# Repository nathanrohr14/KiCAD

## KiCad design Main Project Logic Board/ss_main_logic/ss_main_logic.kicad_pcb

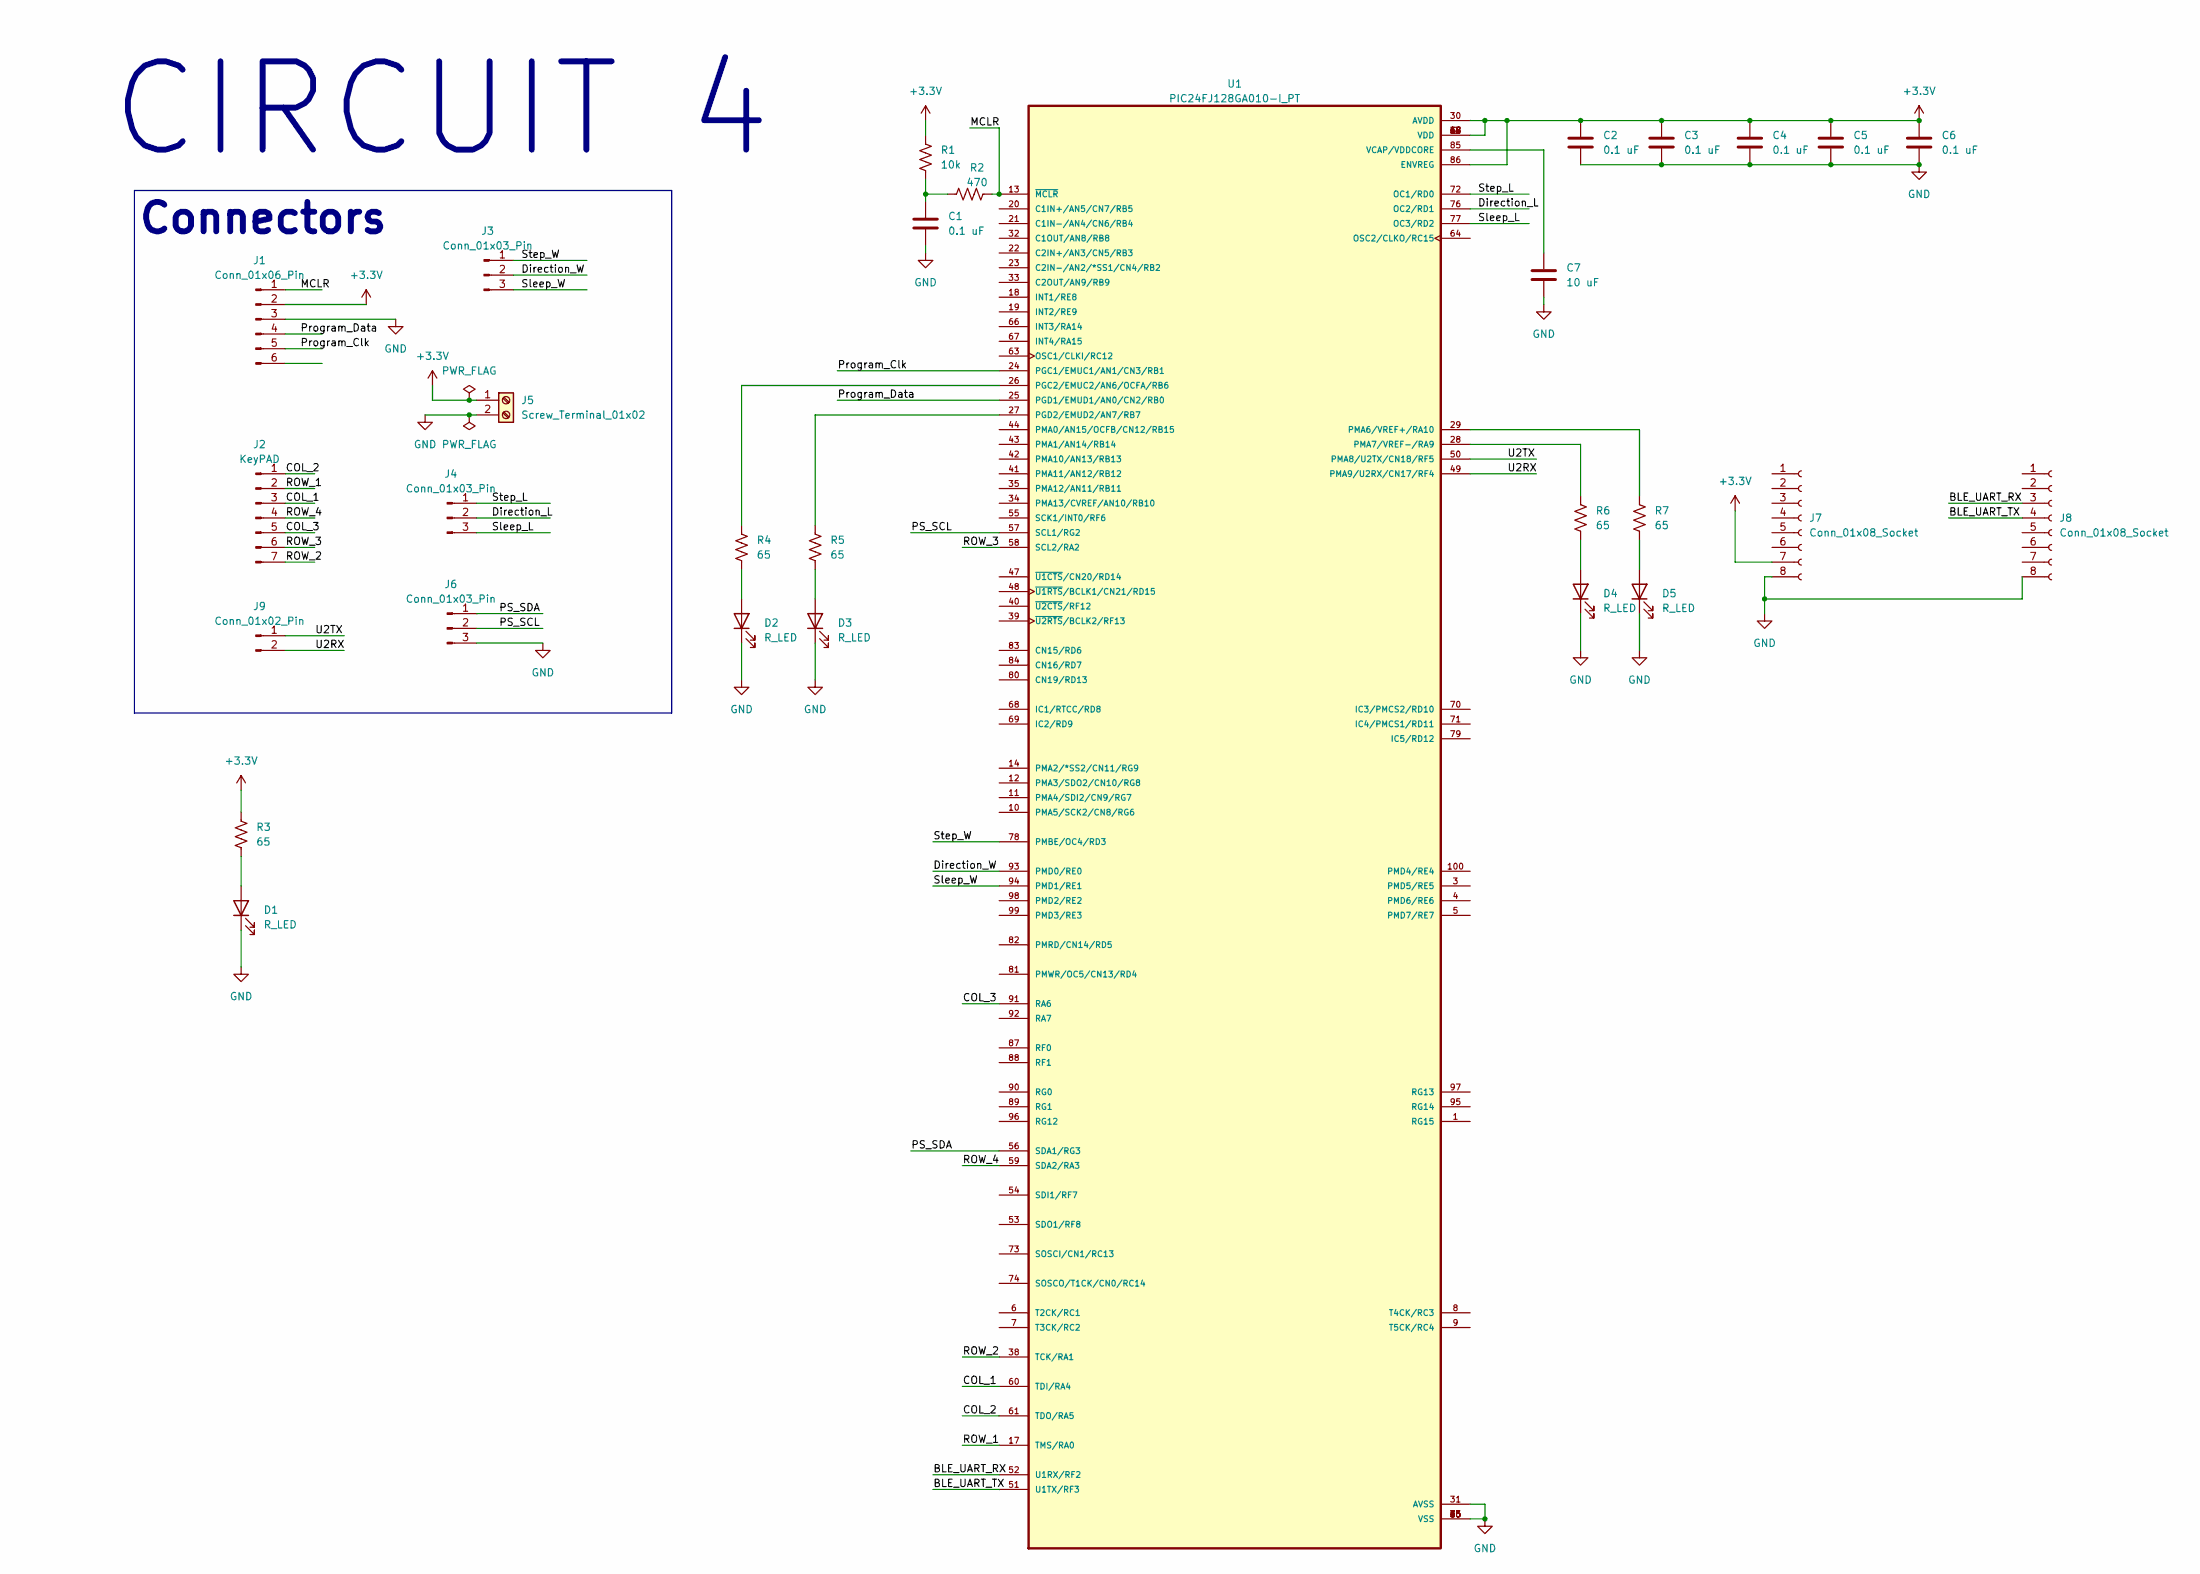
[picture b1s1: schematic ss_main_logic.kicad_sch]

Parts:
C1, C2, C3, C4, C5, C6: 0.1 uF; C_0603_1608Metric; LCSC C14663
C7: 10 uF; C_1206_3216Metric; LCSC C13585
D1, D2, D3, D4, D5: R_LED; LED_0603_1608Metric; LCSC C2286
J1: Conn_01x06_Pin; PinHeader_1x06_P2.54mm_Vertical
J2: KeyPAD; PinHeader_1x07_P2.54mm_Vertical
J3, J4, J6: Conn_01x03_Pin; PinHeader_1x03_P2.54mm_Vertical
J5: Screw_Terminal_01x02; 282837-2_TYC
J7, J8: Conn_01x08_Socket; PinSocket_1x08_P2.54mm_Vertical
J9: Conn_01x02_Pin; PinHeader_1x02_P2.54mm_Vertical
R1: 10k; R_0603_1608Metric
R2: 470; R_0603_1608Metric; LCSC C23179
R3, R4, R5, R6, R7: 65; R_1210_3225Metric; LCSC C11021
U1: PIC24FJ128GA010-I_PT; TQFP-100_14x14mm_P0.5mm; LCSC C638384

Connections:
+3.3V: C2.1, C3.1, C4.1, C5.1, C6.1, J1.2, J5.1, J7.7, R1.1, R3.1, U1.2 (VDD), U1.16 (VDD), U1.30 (AVDD), U1.37 (VDD), U1.46 (VDD), U1.62 (VDD), U1.86 (ENVREG)
/BLE_UART_RX: J8.3, U1.52 (U1RX/RF2)
/BLE_UART_TX: J8.4, U1.51 (U1TX/RF3)
/COL_1: J2.3, U1.60 (TDI/RA4)
/COL_2: J2.1, U1.61 (TDO/RA5)
/COL_3: J2.5, U1.91 (RA6)
/Direction_L: J4.2, U1.76 (OC2/RD1)
/Direction_W: J3.2, U1.93 (PMD0/RE0)
/MCLR: J1.1, R2.2, U1.13 (~MCLR)
/PS_SCL: J6.2, U1.57 (SCL1/RG2)
/PS_SDA: J6.1, U1.56 (SDA1/RG3)
/Program_Clk: J1.5, U1.24 (PGC1/EMUC1/AN1/CN3/RB1)
/Program_Data: J1.4, U1.25 (PGD1/EMUD1/AN0/CN2/RB0)
/ROW_1: J2.2, U1.17 (TMS/RA0)
/ROW_2: J2.7, U1.38 (TCK/RA1)
/ROW_3: J2.6, U1.58 (SCL2/RA2)
/ROW_4: J2.4, U1.59 (SDA2/RA3)
/Sleep_L: J4.3, U1.77 (OC3/RD2)
/Sleep_W: J3.3, U1.94 (PMD1/RE1)
/Step_L: J4.1, U1.72 (OC1/RD0)
/Step_W: J3.1, U1.78 (PMBE/OC4/RD3)
/U2RX: J9.2, U1.49 (PMA9/U2RX/CN17/RF4)
/U2TX: J9.1, U1.50 (PMA8/U2TX/CN18/RF5)
GND: C1.2, C2.2, C3.2, C4.2, C5.2, C6.2, C7.2, D1.1 (K), D2.1 (K), D3.1 (K), D4.1 (K), D5.1 (K), J1.3, J5.2, J6.3, J7.8, J8.8, U1.15 (VSS), U1.31 (AVSS), U1.36 (VSS), U1.45 (VSS), U1.65 (VSS), U1.75 (VSS)
unnamed: C1.1, R1.2, R2.1
unnamed: D1.2 (A), R3.2
unnamed: D2.2 (A), R4.2
unnamed: D3.2 (A), R5.2
unnamed: D4.2 (A), R6.2
unnamed: D5.2 (A), R7.2
unnamed: R4.1, U1.26 (PGC2/EMUC2/AN6/OCFA/RB6)
unnamed: R5.1, U1.27 (PGD2/EMUD2/AN7/RB7)
unnamed: R7.1, U1.29 (PMA6/VREF+/RA10)
unnamed: R6.1, U1.28 (PMA7/VREF-/RA9)
unnamed: C7.1, U1.85 (VCAP/VDDCORE)

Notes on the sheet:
Connectors
CIRCUIT 4

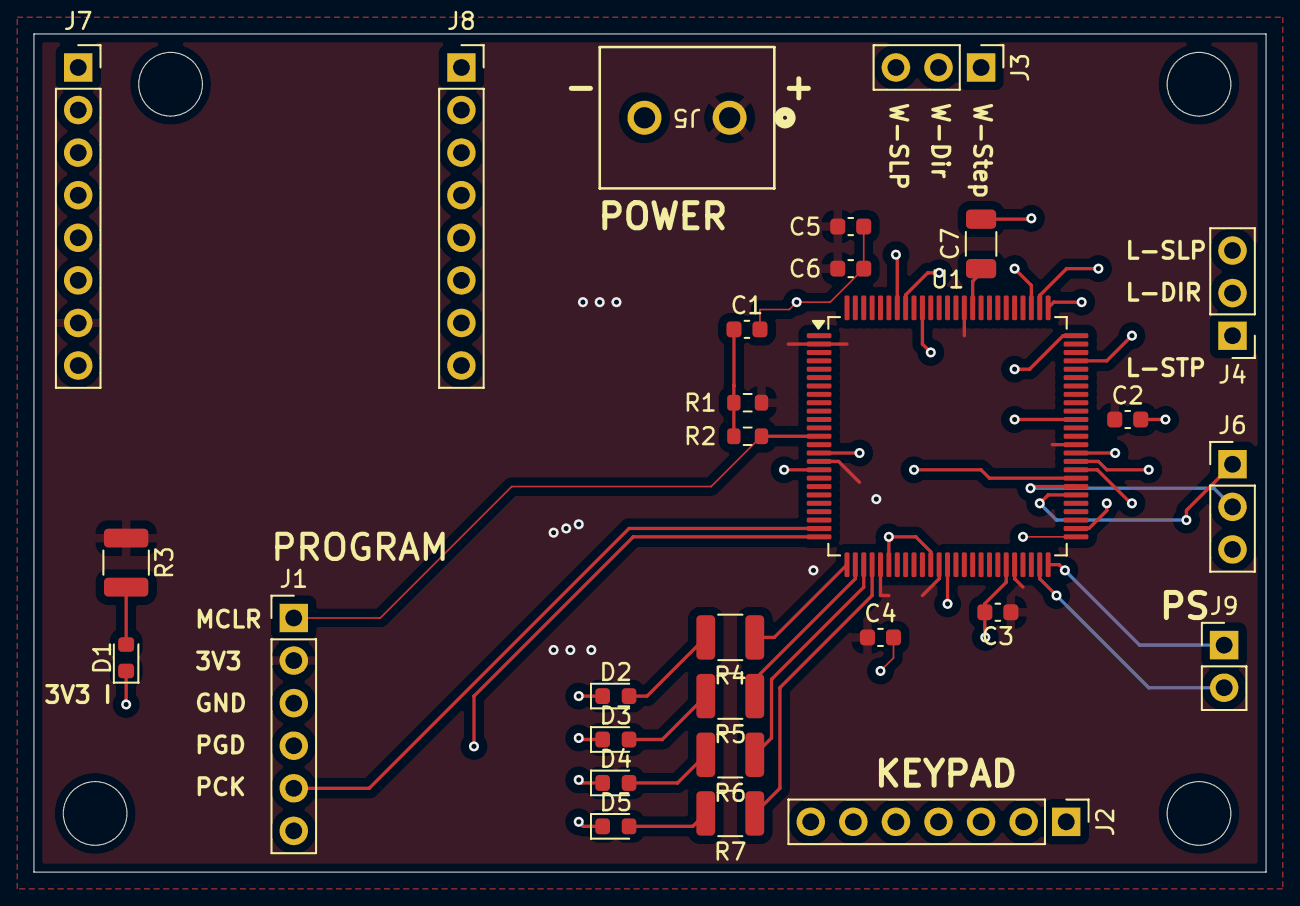
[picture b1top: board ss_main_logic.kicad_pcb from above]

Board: 4 copper layers, 73.5 x 50.0 mm, 29 parts (0 on the bottom side), 35 nets.

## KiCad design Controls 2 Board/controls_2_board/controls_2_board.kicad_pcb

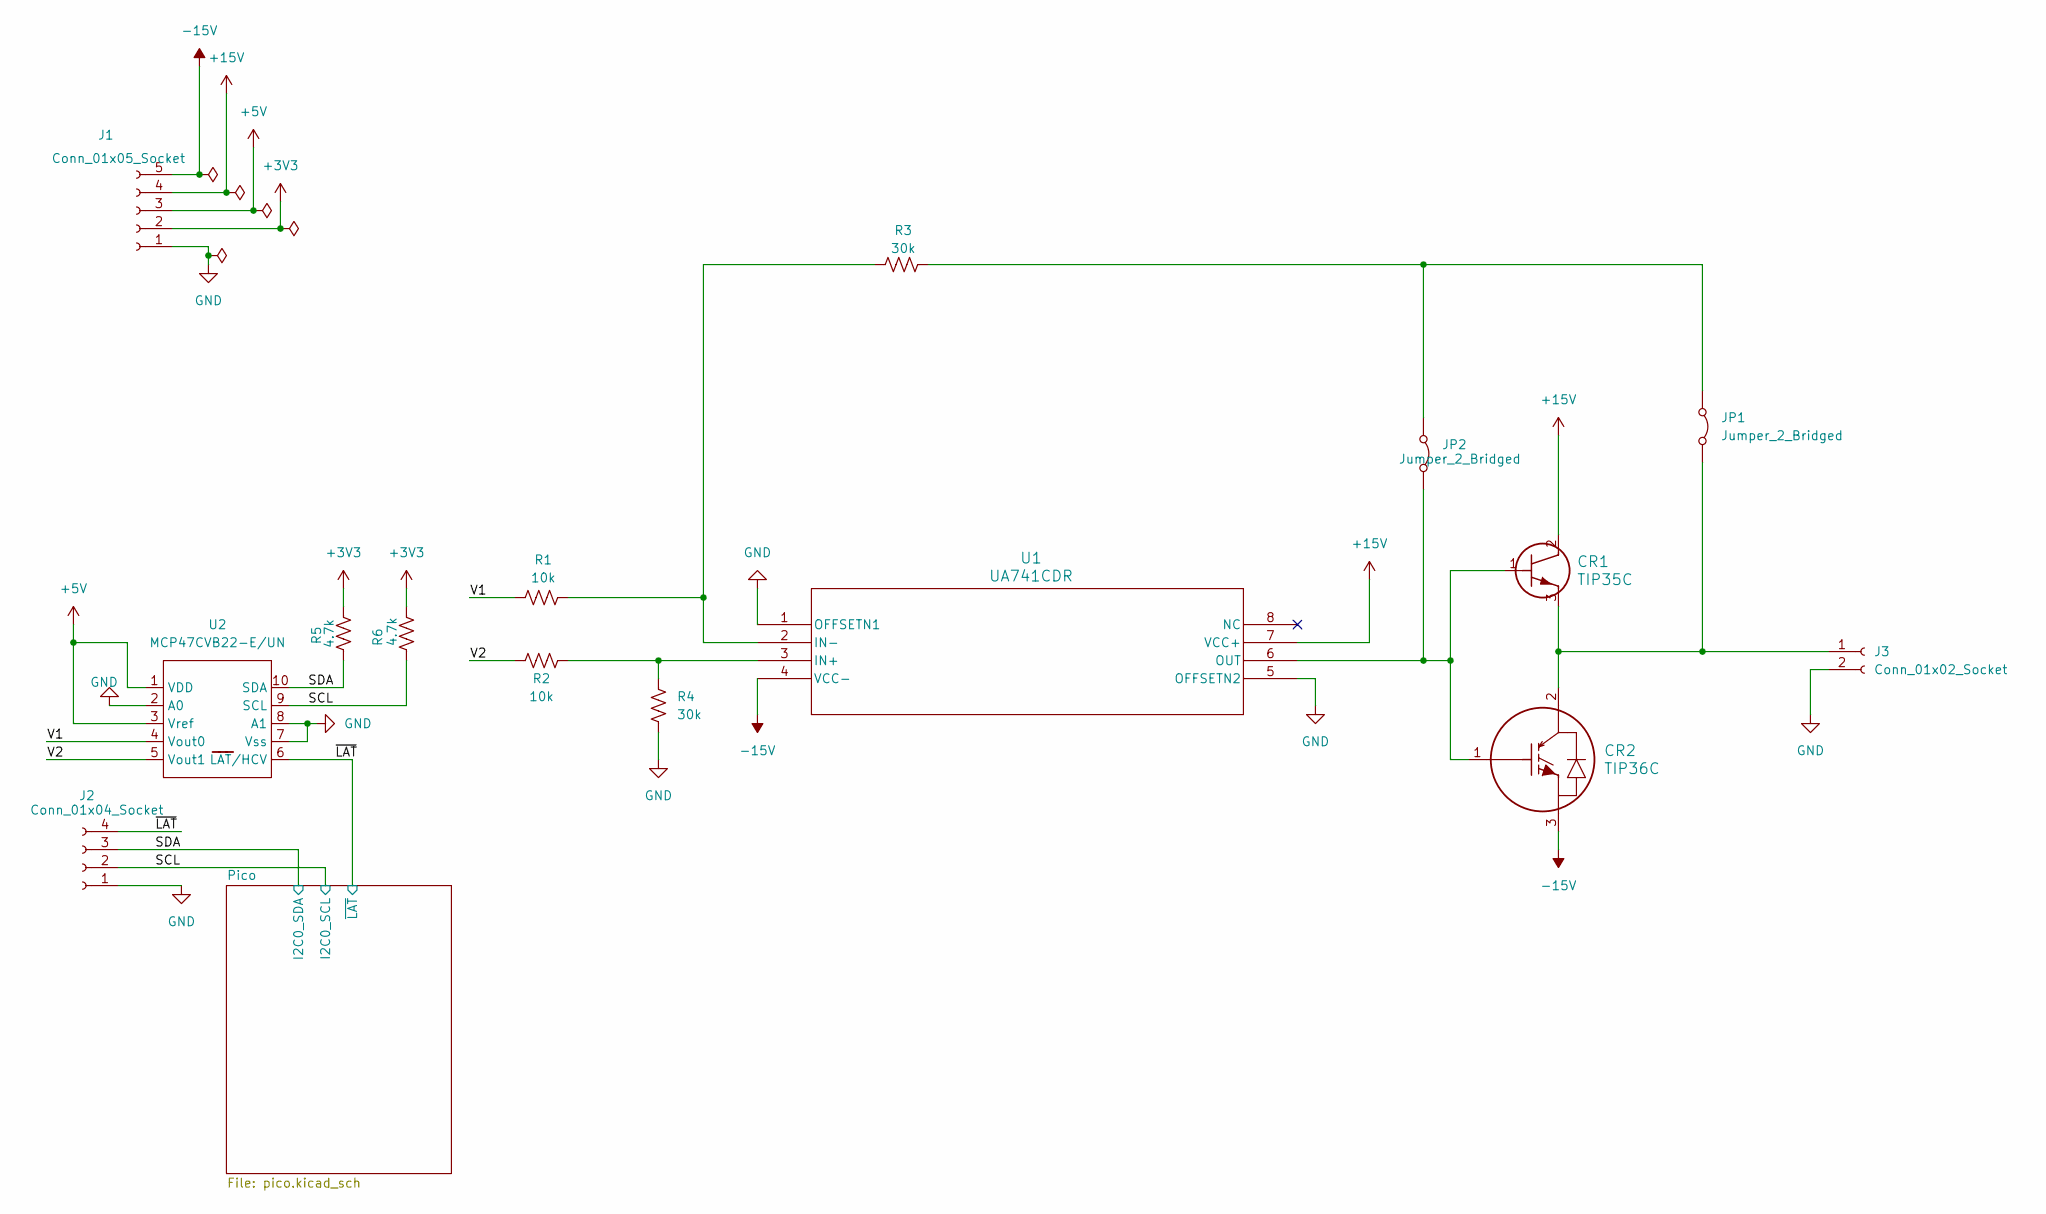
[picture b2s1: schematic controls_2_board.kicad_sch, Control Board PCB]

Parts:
CR1: TIP35C; TO-247_STM
CR2: TIP36C; TO-247_STM
J1: Conn_01x05_Socket; PinSocket_1x05_P2.54mm_Vertical
J2: Conn_01x04_Socket; PinSocket_1x04_P2.54mm_Vertical
J3: Conn_01x02_Socket; PinSocket_1x02_P2.54mm_Vertical
JP1, JP2: Jumper_2_Bridged; TestPoint_2Pads_Pitch2.54mm_Drill0.8mm
R1, R2: 10k; R_Axial_DIN0204_L3.6mm_D1.6mm_P7.62mm_Horizontal
R3, R4: 30k; R_Axial_DIN0204_L3.6mm_D1.6mm_P7.62mm_Horizontal
R5, R6: 4.7k; R_Axial_DIN0204_L3.6mm_D1.6mm_P7.62mm_Horizontal
U1: UA741CDR; D8; LCSC C2057458
U2: MCP47CVB22-E/UN; MSOP-10_3x3mm_P0.5mm

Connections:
+3V3: J1.2, R5.2, R6.2; also elsewhere on the board
+5V: J1.3, U2.1 (VDD), U2.3 (Vref)
+15V: CR1.2, J1.4, U1.7 (VCC+)
-15V: CR2.3, J1.5, U1.4 (VCC-)
/SCL: J2.2, R6.1, U2.9 (SCL); also elsewhere on the board
/SDA: J2.3, R5.1, U2.10 (SDA); also elsewhere on the board
/V1: R1.1, U2.4 (Vout0)
/V2: R2.2, U2.5 (Vout1)
/~LAT: J2.4, U2.6 (LAT/HCV); also elsewhere on the board
GND: J1.1, J2.1, J3.2, R4.2, U1.1 (OFFSETN1), U1.5 (OFFSETN2), U2.2 (A0), U2.7 (Vss), U2.8 (A1); also elsewhere on the board
unnamed: CR1.3, CR2.2, J3.1, JP1.2 (B)
unnamed: JP1.1 (A), JP2.1 (A), R3.2
unnamed 12: CR1.1, CR2.1, JP2.2 (B), U1.6 (OUT); also elsewhere on the board
unnamed: R2.1, R4.1, U1.3 (IN+)
unnamed: R1.2, R3.1, U1.2 (IN-)

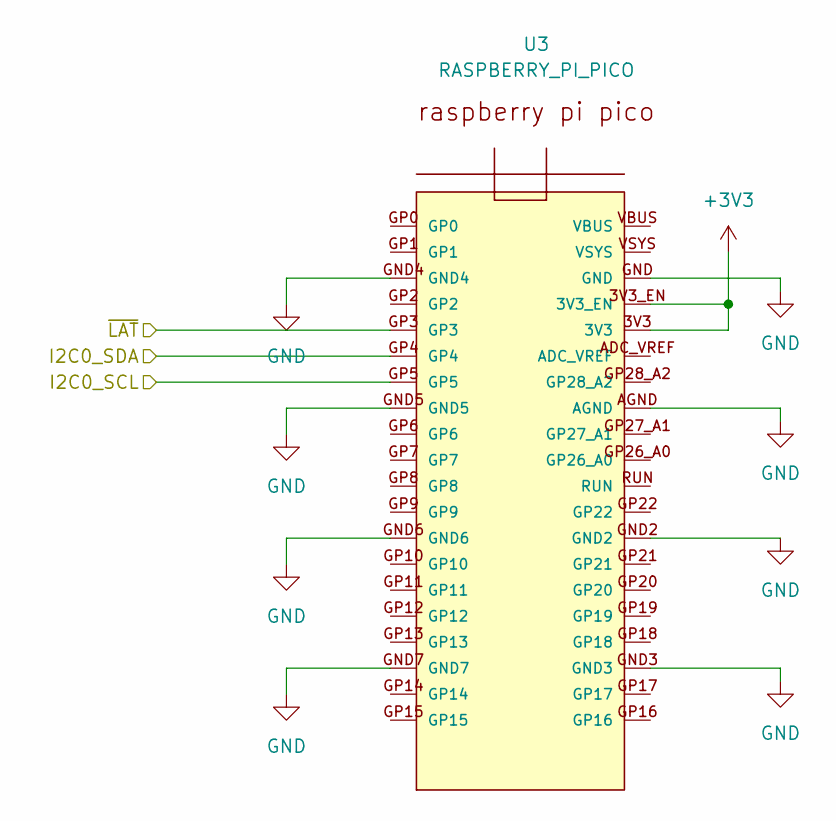
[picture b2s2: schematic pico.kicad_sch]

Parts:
U3: RASPBERRY_PI_PICO

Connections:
+3V3: U3.3V3, U3.3V3_EN; also elsewhere on the board
/SCL: U3.GP5; also elsewhere on the board
/SDA: U3.GP4; also elsewhere on the board
/~LAT: U3.GP3; also elsewhere on the board
GND: U3.AGND, U3.GND, U3.GND2, U3.GND3, U3.GND4, U3.GND5, U3.GND6, U3.GND7; also elsewhere on the board

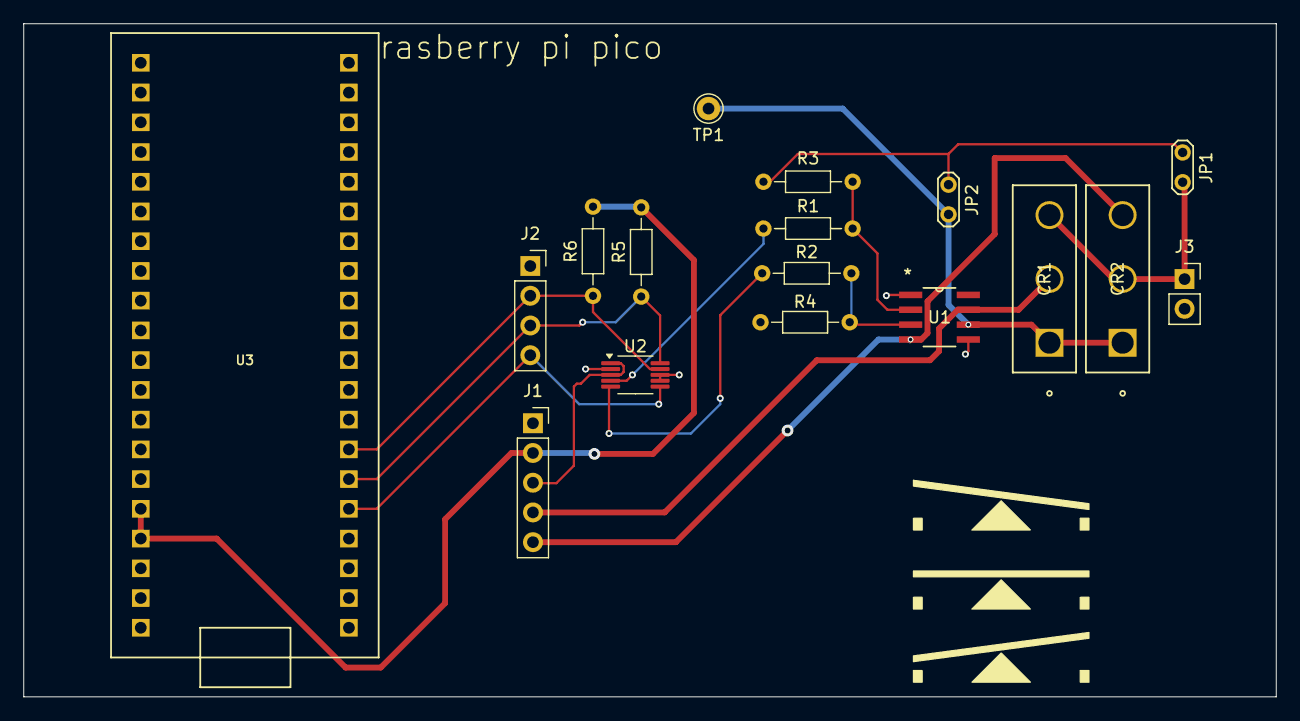
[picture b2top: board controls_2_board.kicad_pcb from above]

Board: 2 copper layers, 107.0 x 57.5 mm, 17 parts (0 on the bottom side), 15 nets.

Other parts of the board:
TP1: TestPoint; Pin_D1.0mm_L10.0mm

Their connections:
unnamed 12: TP1.1; also elsewhere on the board

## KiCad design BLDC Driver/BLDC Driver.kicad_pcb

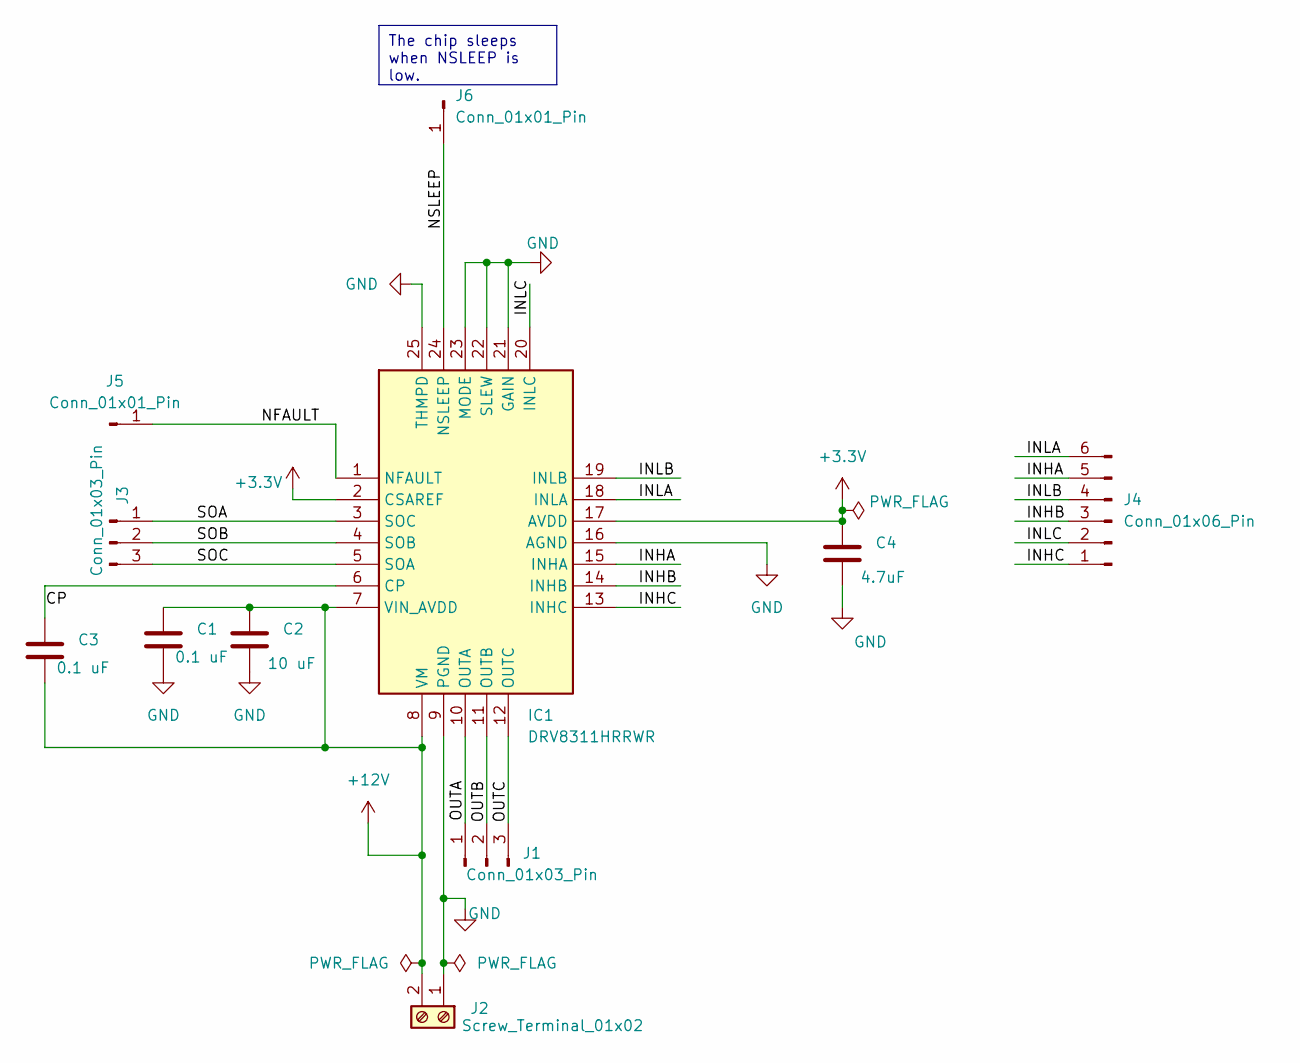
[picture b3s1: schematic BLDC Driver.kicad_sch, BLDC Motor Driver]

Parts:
C1: 0.1 uF; C0603X5R160-104MNP; Manufacter Part Number C0603X5R160-104MNP
C2: 10 uF; CAP_CL21_SAM-M; Manufacter Part Number CL21A106KOQNNNE
C3: 0.1 uF; C0603X5R160-104MNP; Manufacturer Part Number C0603X5R160-104MNP
C4: 4.7uF; CAP_CL10_SAM; Manufacturer Part Number CL10A475KQ8NNNC
IC1: DRV8311HRRWR; Mouser Part Number 595-DRV8311HRRWR
J1, J3: Conn_01x03_Pin; PinHeader_1x03_P2.54mm_Vertical
J2: Screw_Terminal_01x02; CONN2_710002_WRE
J4: Conn_01x06_Pin; PinHeader_1x06_P2.54mm_Vertical
J5, J6: Conn_01x01_Pin; PinHeader_1x01_P2.54mm_Vertical

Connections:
+3.3V: C4.1, IC1.2 (CSAREF), IC1.17 (AVDD)
+12V: C1.1, C2.1, C3.2, IC1.7 (VIN_AVDD), IC1.8 (VM), J2.2
/CP: C3.1, IC1.6 (CP)
/INHA: IC1.15 (INHA), J4.5
/INHB: IC1.14 (INHB), J4.3
/INHC: IC1.13 (INHC), J4.1
/INLA: IC1.18 (INLA), J4.6
/INLB: IC1.19 (INLB), J4.4
/INLC: IC1.20 (INLC), J4.2
/NFAULT: IC1.1 (NFAULT), J5.1
/NSLEEP: IC1.24 (NSLEEP), J6.1
/OUTA: IC1.10 (OUTA), J1.1
/OUTB: IC1.11 (OUTB), J1.2
/OUTC: IC1.12 (OUTC), J1.3
/SOA: IC1.3 (SOC), J3.1
/SOB: IC1.4 (SOB), J3.2
/SOC: IC1.5 (SOA), J3.3
GND: C1.2, C2.2, C4.2, IC1.9 (PGND), IC1.16 (AGND), IC1.21 (GAIN), IC1.22 (SLEW), IC1.23 (MODE), IC1.25 (NSLEEP), J2.1

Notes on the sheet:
The chip sleeps when NSLEEP is low.

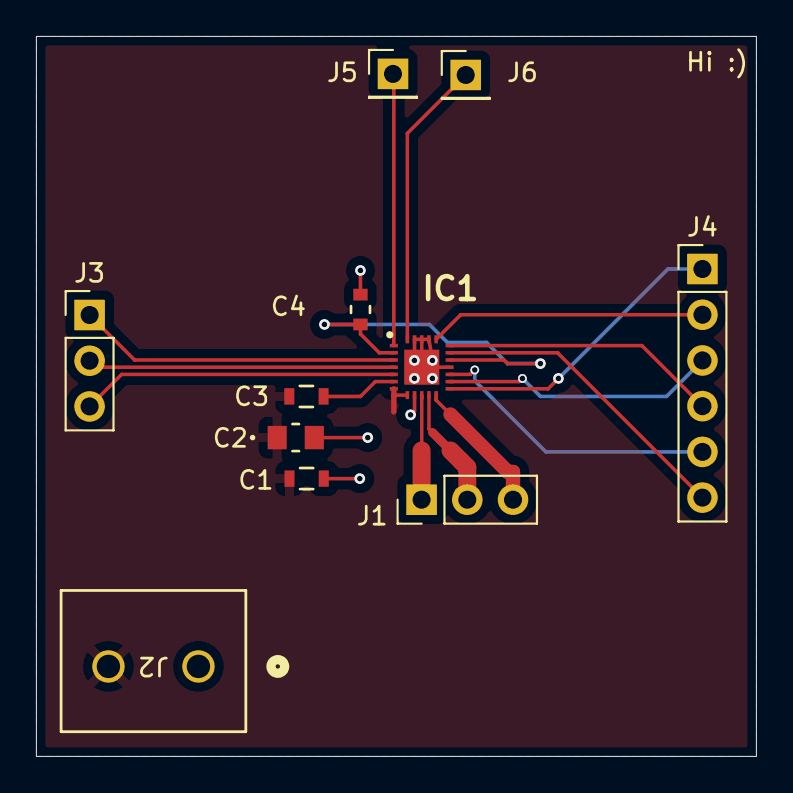
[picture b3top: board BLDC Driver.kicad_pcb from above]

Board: 2 copper layers, 40.0 x 40.0 mm, 11 parts (0 on the bottom side), 18 nets.

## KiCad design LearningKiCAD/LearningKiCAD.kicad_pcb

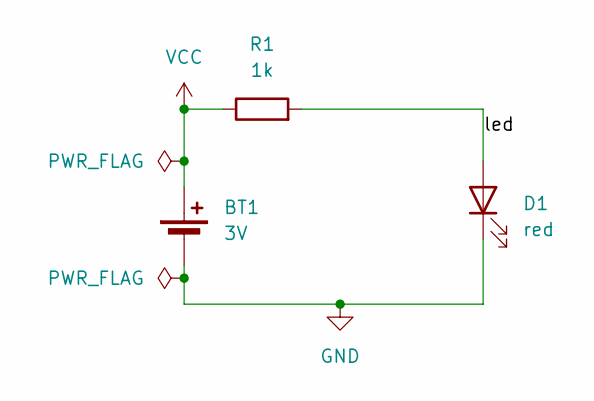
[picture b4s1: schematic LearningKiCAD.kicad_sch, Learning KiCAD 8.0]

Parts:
BT1: 3V; BatteryHolder_Keystone_1058_1x2032
D1: red; LED_D5.0mm
R1: 1k; R_Axial_DIN0309_L9.0mm_D3.2mm_P12.70mm_Horizontal

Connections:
/led: D1.2 (A), R1.2
GND: BT1.2 (-), D1.1 (K)
VCC: BT1.1 (+), R1.1

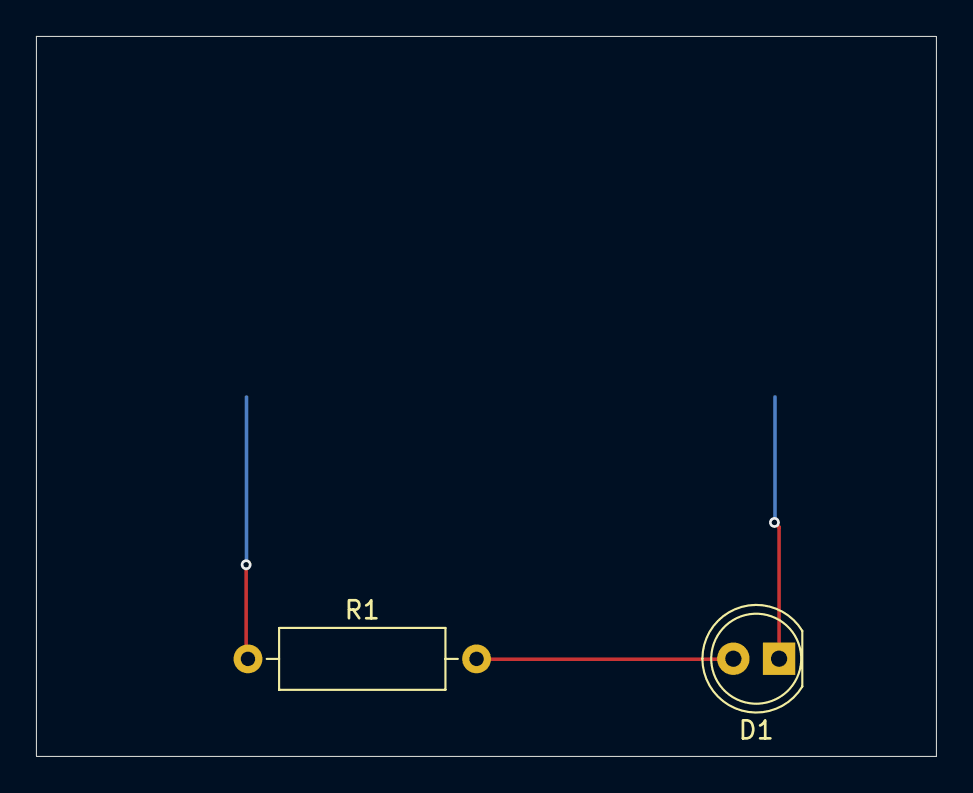
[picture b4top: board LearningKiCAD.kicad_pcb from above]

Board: 2 copper layers, 50.0 x 40.0 mm, 3 parts (1 on the bottom side), 3 nets.

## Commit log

2025-02-21 Just looking
2025-03-04 Added pico
2025-03-06 Altered PICO
2025-03-11 Added different BLE and LEDs
2025-03-12 Added some gerbers
2025-03-12 Track all files
